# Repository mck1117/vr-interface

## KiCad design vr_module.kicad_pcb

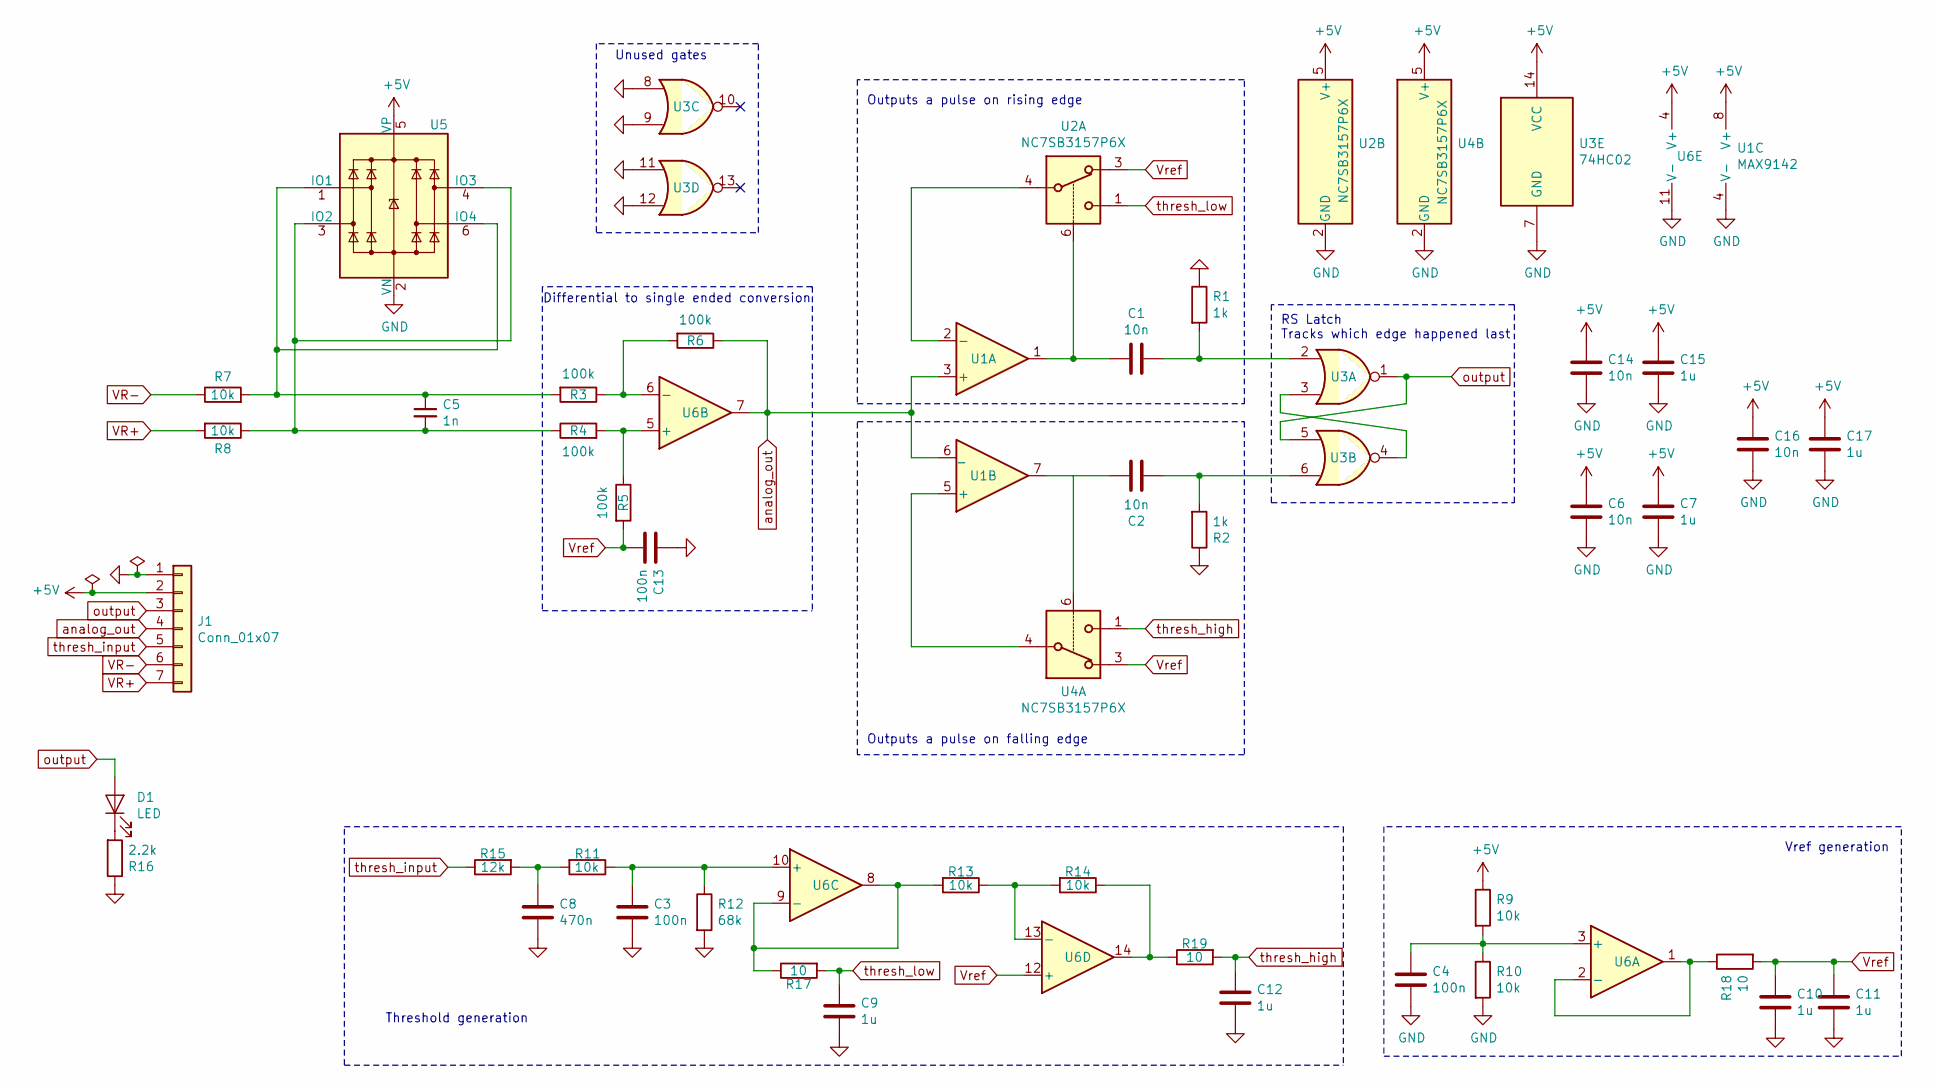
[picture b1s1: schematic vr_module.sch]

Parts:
C1, C2, C6, C14, C16: 10n; C_0402_1005Metric; LCSC C15195
C3, C4, C13: 100n; C_0402_1005Metric; LCSC C1525
C5: 1n; C_0402_1005Metric; LCSC C1523
C7, C9, C10, C11, C12, C15, C17: 1u; C_0402_1005Metric; LCSC C52923
C8: 470n; C_0402_1005Metric; LCSC C47339
D1: LED; LED_0603_1608Metric; LCSC C72043
J1: Conn_01x07; PinHeader_1x07_P2.54mm_Vertical
R1, R2: 1k; R_0402_1005Metric; LCSC C11702
R3, R4, R5, R6: 100k; R_0402_1005Metric; LCSC C25741
R7, R8: 10k; R_0805_2012Metric; LCSC C17414
R9, R10, R11, R13, R14: 10k; R_0402_1005Metric; LCSC C25744
R12: 68k; R_0402_1005Metric; LCSC C36871
R15: 12k; R_0402_1005Metric; LCSC C25752
R16: 2.2k; R_0402_1005Metric; LCSC C25879
R17, R18, R19: 10; R_0402_1005Metric; LCSC C25077
U1: MAX9142; SOIC-8_3.9x4.9mm_P1.27mm; LCSC C18567
U2, U4: NC7SB3157P6X; SOT-363_SC-70-6; LCSC C87403
U3: 74HC02; SOIC-14_3.9x8.7mm_P1.27mm; LCSC C5588
U5: SRV05-4; SOT-23-6; LCSC C85364
U6: MCP6004; TSSOP-14_4.4x5mm_P0.65mm; LCSC C50282

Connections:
+5V: C6.1, C7.1, C14.1, C15.1, C16.1, C17.1, J1.2, R9.1, U1.8 (V+), U2.5 (V+), U3.14 (VCC), U4.5 (V+), U5.5 (VP), U6.4 (V+)
GND: C3.2, C4.2, C6.2, C7.2, C8.2, C9.2, C10.2, C11.2, C12.2, C13.1, C14.2, C15.2, C16.2, C17.2, J1.1, R1.1, R2.1, R10.2, R12.2, R16.1, U1.4 (V-), U2.2 (GND), U3.7 (GND), U3.8, U3.9, U3.11, U3.12, U4.2 (GND), U5.2 (VN), U6.11 (V-)
unnamed: C1.1, R1.2, U3.2
unnamed: C1.2, U1.1, U2.6
unnamed: C2.1, R2.2, U3.6
unnamed: C2.2, U1.7, U4.6
unnamed: C3.1, R11.1, R12.1, U6.10 (+)
unnamed: C4.1, R9.2, R10.1, U6.3 (+)
unnamed: C5.1, R3.2, R7.2, U5.1 (IO1), U5.6 (IO4)
unnamed: C5.2, R4.1, R8.1, U5.3 (IO2), U5.4 (IO3)
unnamed: C8.1, R11.2, R15.2
unnamed: D1.1 (K), R16.2
unnamed: R3.1, R6.2, U6.6 (-)
unnamed: R4.2, R5.1, U6.5 (+)
unnamed: R13.1, R14.2, U6.13 (-)
unnamed: R13.2, R17.1, U6.8, U6.9 (-)
unnamed: R14.1, R19.1, U6.14
unnamed: R18.1, U6.1, U6.2 (-)
unnamed: U1.2 (-), U2.4
unnamed: U1.5 (+), U4.4
unnamed: U3.3, U3.4
VR+: J1.7, R8.2
VR-: J1.6, R7.1
Vref: C10.1, C11.1, C13.2, R5.2, R18.2, U2.3, U4.3, U6.12 (+)
analog_out: J1.4, R6.1, U1.3 (+), U1.6 (_), U6.7
output: D1.2 (A), J1.3, U3.1, U3.5
thresh_high: C12.1, R19.2, U4.1
thresh_input: J1.5, R15.1
thresh_low: C9.1, R17.2, U2.1

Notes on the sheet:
Outputs a pulse on rising edge
Outputs a pulse on falling edge
Differential to single ended conversion
RS Latch Tracks which edge happened last
Unused gates
Vref generation
Threshold generation

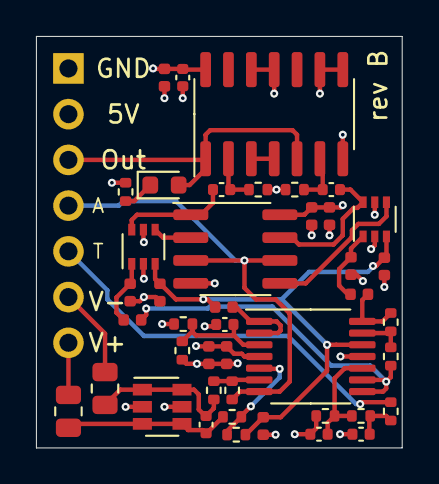
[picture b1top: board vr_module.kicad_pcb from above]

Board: 4 copper layers, 20.3 x 22.9 mm, 44 parts (1 on the bottom side), 29 nets.

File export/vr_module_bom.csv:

Comment,Designator,Footprint,LCSC
10n,"C1,C2,C6,C9,C10",Capacitor_SMD:C_0402_1005Metric,C15195
100n,"C3,C4",Capacitor_SMD:C_0402_1005Metric,C1525
1n,C5,Capacitor_SMD:C_0402_1005Metric,C1523
1u,C7,Capacitor_SMD:C_0603_1608Metric,C15849
470n,C8,Capacitor_SMD:C_0402_1005Metric,C47339
LED,D1,LED_SMD:LED_0603_1608Metric,C72043
Conn_01x07,J1,Connector_PinHeader_2.54mm:PinHeader_1x07_P2.54mm_Vertical,
1k,"R1,R2",Resistor_SMD:R_0402_1005Metric,C11702
10k,"R11,R13,R14,R10,R9",Resistor_SMD:R_0402_1005Metric,C25744
68k,R12,Resistor_SMD:R_0402_1005Metric,C36871
12k,R15,Resistor_SMD:R_0402_1005Metric,C25752
2.2k,R16,Resistor_SMD:R_0402_1005Metric,C25879
100k,"R6,R5,R4,R3",Resistor_SMD:R_0402_1005Metric,C25741
10k,"R7,R8",Resistor_SMD:R_0805_2012Metric,C17414
MAX9142,U1,Package_SO:SOIC-8_3.9x4.9mm_P1.27mm,C18567
NC7SB3157P6X,"U2,U4",Package_TO_SOT_SMD:SOT-363_SC-70-6,C87403
74HC00,U3,Package_SO:SOIC-14_3.9x8.7mm_P1.27mm,C5586
SRV05-4,U5,Package_TO_SOT_SMD:SOT-23-6,C85364
MCP6004,U6,Package_SO:TSSOP-14_4.4x5mm_P0.65mm,C50282

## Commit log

2021-01-04 gitignore
2021-01-04 add board
2021-01-04 add power caps, silk on bottom
2021-01-04 filter pwm harder
2021-01-05 lcsc numbers, optimize divider
2021-01-05 add filter caps
2021-01-05 ground unused inputs to NAND
2021-01-05 upgrade comparator
2021-01-05 I heard we like LEDs
2021-01-05 oh no one comparator was flipped
2021-01-22 export
2021-02-04 rev b improvements
2021-03-27 rev b export
2021-09-03 add spice model
2021-09-03 gitignore, tweaks
